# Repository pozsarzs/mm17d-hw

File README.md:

## MM17D * RH/T measuring device  
Copyright (C) 2023 Pozsár Zsolt <pozsarzs@gmail.com>  
Homepage: <http://www.pozsarzs.hu>  
GitHub: <https://github.com/pozsarzs/mm17d-hw>

#### Documentation
|features               |             |
|:----------------------|-------------|
|hardware version       |v231006      |
|documentation version  |v1.0         |
|documentation language |en           |
|documentation licence  |CC-BY-NC-4.0 |

#### Not own documentation in the package
 - PP42 box by [Supertronic S.A.](https://supertronic.com/)

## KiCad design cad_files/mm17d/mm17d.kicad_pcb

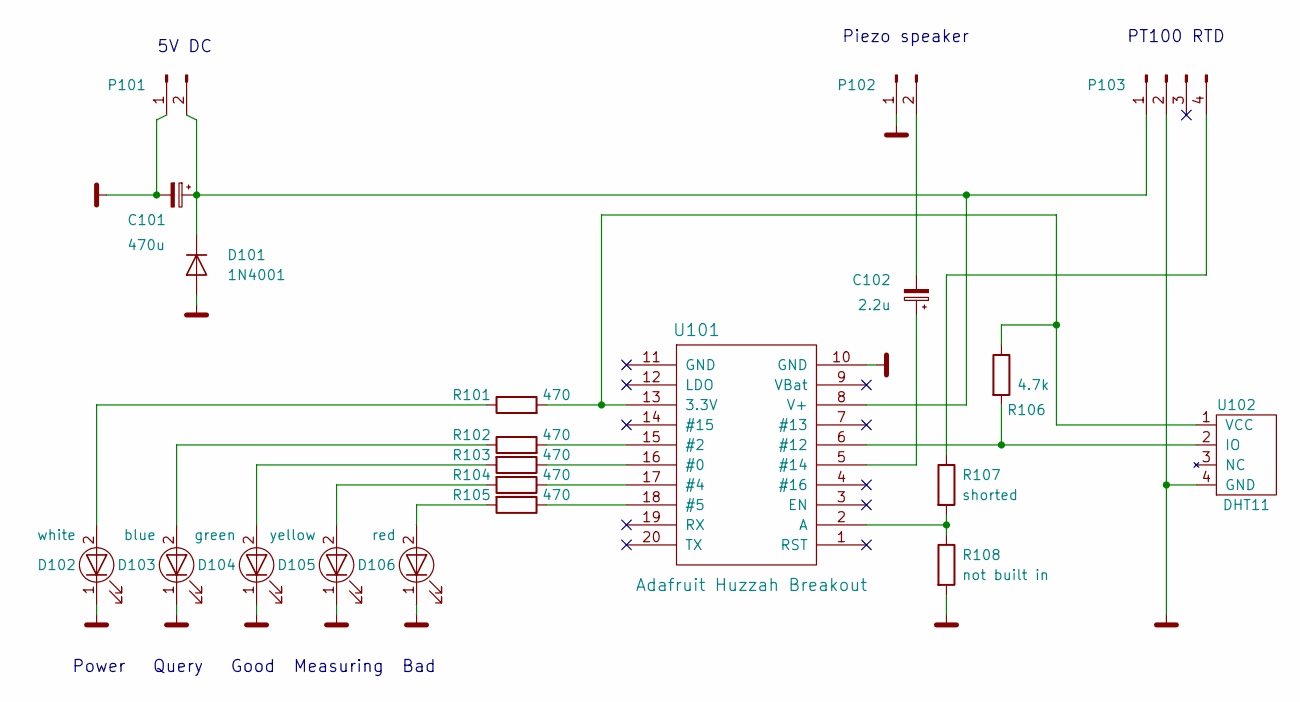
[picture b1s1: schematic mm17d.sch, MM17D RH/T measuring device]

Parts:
C101: 470u; CP_Radial_D8.0mm_P3.50mm
C102: 2.2u; C_Rect_L7.0mm_W4.5mm_P5.00mm
D101: 1N4001; Diode_DO-41_SOD81_Horizontal_RM10
D102: white; LED_D3.0mm
D103: blue; LED_D3.0mm
D104: green; LED_D3.0mm
D105: yellow; LED_D3.0mm
D106: red; LED_D3.0mm
P101, P102: Conn_01x02_Male; PinHeader_1x02_P2.54mm_Vertical
P103: Conn_01x04_Male; PinHeader_1x04_P2.54mm_Vertical
R101, R102, R103, R104, R105: 470; Resistor_Horizontal_RM7mm
R106: 4.7k; Resistor_Horizontal_RM7mm
R107: shorted; Resistor_Horizontal_RM10mm
R108: not built in; Resistor_Horizontal_RM10mm
U101: Adafruit Huzzah Breakout; Adafruit_Huzzah_Breakout
U102: DHT11; Aosong_DHT11_5.5x12.0_P2.54mm

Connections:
GND: C101.2, D101.2 (A), D102.1 (K), D103.1 (K), D104.1 (K), D105.1 (K), D106.1 (K), P101.1, P102.1, P103.2, R108.2, U101.10 (GND), U102.4 (GND)
unnamed: C101.1, D101.1 (K), P101.2, P103.1, U101.8 (V+)
unnamed: C102.1, U101.5 (#14)
unnamed: C102.2, P102.2
unnamed: D102.2 (A), R101.1
unnamed: D103.2 (A), R102.1
unnamed: D104.2 (A), R103.2
unnamed: D105.2 (A), R104.2
unnamed: D106.2 (A), R105.2
unnamed: P103.4, R107.1
unnamed: R101.2, R106.1, U101.13 (3.3V), U102.1 (VCC)
unnamed: R102.2, U101.15 (#2)
unnamed: R103.1, U101.16 (#0)
unnamed: R104.1, U101.17 (#4)
unnamed: R105.1, U101.18 (#5)
unnamed: R106.2, U101.6 (#12), U102.2 (IO)
unnamed: R107.2, R108.1, U101.2 (A)

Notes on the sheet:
Power Query Good Measuring Bad
5V DC
Piezo speaker
PT100 RTD

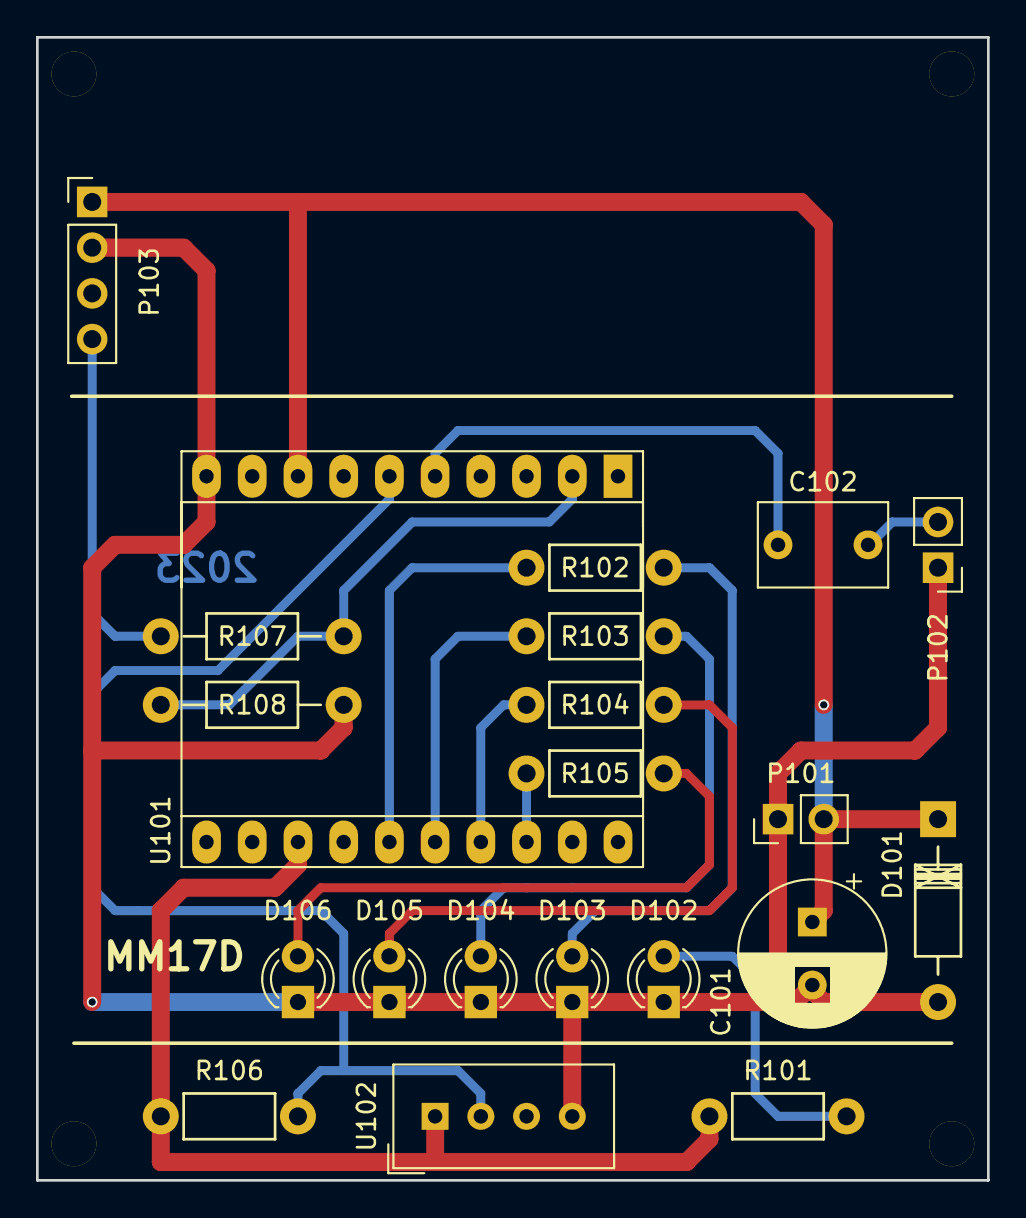
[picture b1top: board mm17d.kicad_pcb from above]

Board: 2 copper layers, 52.8 x 63.5 mm, 21 parts (0 on the bottom side), 17 nets.

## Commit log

2023-10-13 231013
2023-10-15 231015
2023-10-22 231022
